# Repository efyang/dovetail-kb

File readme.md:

# Dovetail Keyboard

Uses a modified version of ergogen that supports placing arbitrary library parts.

### FreeCAD Pics (some parts didn't survive the conversion process)

## Features

-   underglow
-   trackpad (tm035035-2024-003)
-   solder-on 90-degree thumb clusters
-   choc spacing
-   36 keys

To update using ergogen:

-   `node ergogen/src/cli.js ergogen.yaml -o .`
-   Open pcb in pcbnew
-   Tools -> Update Footprints from Library
-   Check all "Update Options"
-   Update

## Parts list

| Qty | Part                       | Info                                                                                          | Link(s)                                                   |     |
| --- | -------------------------- | --------------------------------------------------------------------------------------------- | --------------------------------------------------------- | --- |
| 2   | KB2040                     | QMK compatible pro-micro footprint. Currently must have QMK for trackpad, recommmended RP2040 | https://www.adafruit.com/product/5302                     |     |
| 2   | PJ-320A Jack               |                                                                                               | https://www.aliexpress.com/item/2251832181971069.html     |     |
| 36  | Kailh Choc Hotswap Sockets |                                                                                               | https://www.aliexpress.com/item/3256803389452947.html     |     |
| 3   | M2 Standoffs               | Trying M2x7                                                                                   | https://www.aliexpress.com/item/2251832782516182.html     |     |
| idk can't count   | M2 Screws                  |                                                                                               |                                                           |     |
| 1   | FPC Cable                  | 0.5mm pitch, 12pin, same side (but probably should cut and strip yourself anyways)            | https://www.aliexpress.com/item/3256801417741263.html     |     |
| 1   | FPC Connector              | 12P, 0.5mm pitch                                                                              | https://www.aliexpress.com/item/2261800162045502.html     |     |
| 4   | MCU Sockets (optional)     | I like these ones - PH3.5, use them with regular headers                                      | https://www.aliexpress.com/item/2251832713321083.html     |     |
| 2   | Scroll Wheel               |                                                                                               | https://www.aliexpress.com/item/2251832804635444.html     |     |
| 14  | WS2812b 5050               |                                                                                               | https://www.aliexpress.com/item/3256802466699315.html     |     |
| 1   | TM035035-2024-003 Trackpad | Cirque Glide Trackpad with overlay                                                            | https://www.mouser.com/ProductDetail/355-TM0350352024-003 |     |
| 2   | EVQ-P7C01P Reset Switch    | I wanted to be fancy lol                                                                      | https://www.mouser.com/ProductDetail/667-EVQP7C01P        |     |
| 1   | Trackpad holder part       | Probably want 2 just in case                                                                  | [In repo](Models/trackpad-holder-Fusion.stl)              |     |
| 1   | 1 of each PCB minimum      | left-main, right-main, left-thumb, right-thumb (you could actually interchange the thumbs)    | [In repo](gerbers)                                        |     |
| 2   | Plates        | Untested                                                                                           | [In repo](outlines/cutout_with_holes.dxf)                                                          |     |
| 12   | M2 standoffs (5mm)         | Untested                                                                                           | https://www.aliexpress.com/item/2251832782591461.html                                                          |     |
| 2  | 1/4in lock nut         | Untested                                                                                           | https://www.aliexpress.com/item/3256802483856268.html                                                          |     |
| 2  | Camera swivel thingy        | Untested                                                                                           | https://www.aliexpress.com/item/3256803400603212.html                                                          |     |
| 2  | Magnetic Base        | Untested                                                                                           | https://www.aliexpress.com/item/3256803496352836.html                                                          |     |
| 2  | Palm LED Diffuser | Untested                                                                                           | [In repo](outlines/palm_led_diffuser_final.dxf)                                                          |     |
| 2  | Palm LED Diffuser Spacer | Untested                                                                                           | [In repo](outlines/palm_led_diffuser_spacer.dxf)                                                          |     |
| 36  | Diodes           |                                                                                               |      |     |
| 1   | Case (optional)            |                                                                                               | https://www.aliexpress.com/item/3256803532895347.html     |     |

## Notes

-   Designed for 3.3v power/logic (kb2040)
    -   if you want to use 5v then you have to desolder more on the trackpad pcb
-   Rectangular size (at most): ~ 14cmx11cmx5.5cm

## Inspo/Useful Links
- https://www.reddit.com/r/ErgoMechKeyboards/comments/uq2yyq/kyria_with_cirque_circle_trackpad/
- https://github.com/macroxue/keyboard-tenting
- https://www.reddit.com/r/PeripheralDesign/comments/uk9l94/trackball_emulation_on_cirque_glidepoint_circle/
- https://www.cirque.com/message-board?p=post%2Fusing-the-cirque-tm035035-and-tm040040-circle-trackpads-in-5v-systems-10126328
- https://github.com/dkao/qmk_firmware/commits/cirque_trackpad_features
- https://www.thingiverse.com/thing:5385829/files
- https://github.com/Bastardkb/dilemma

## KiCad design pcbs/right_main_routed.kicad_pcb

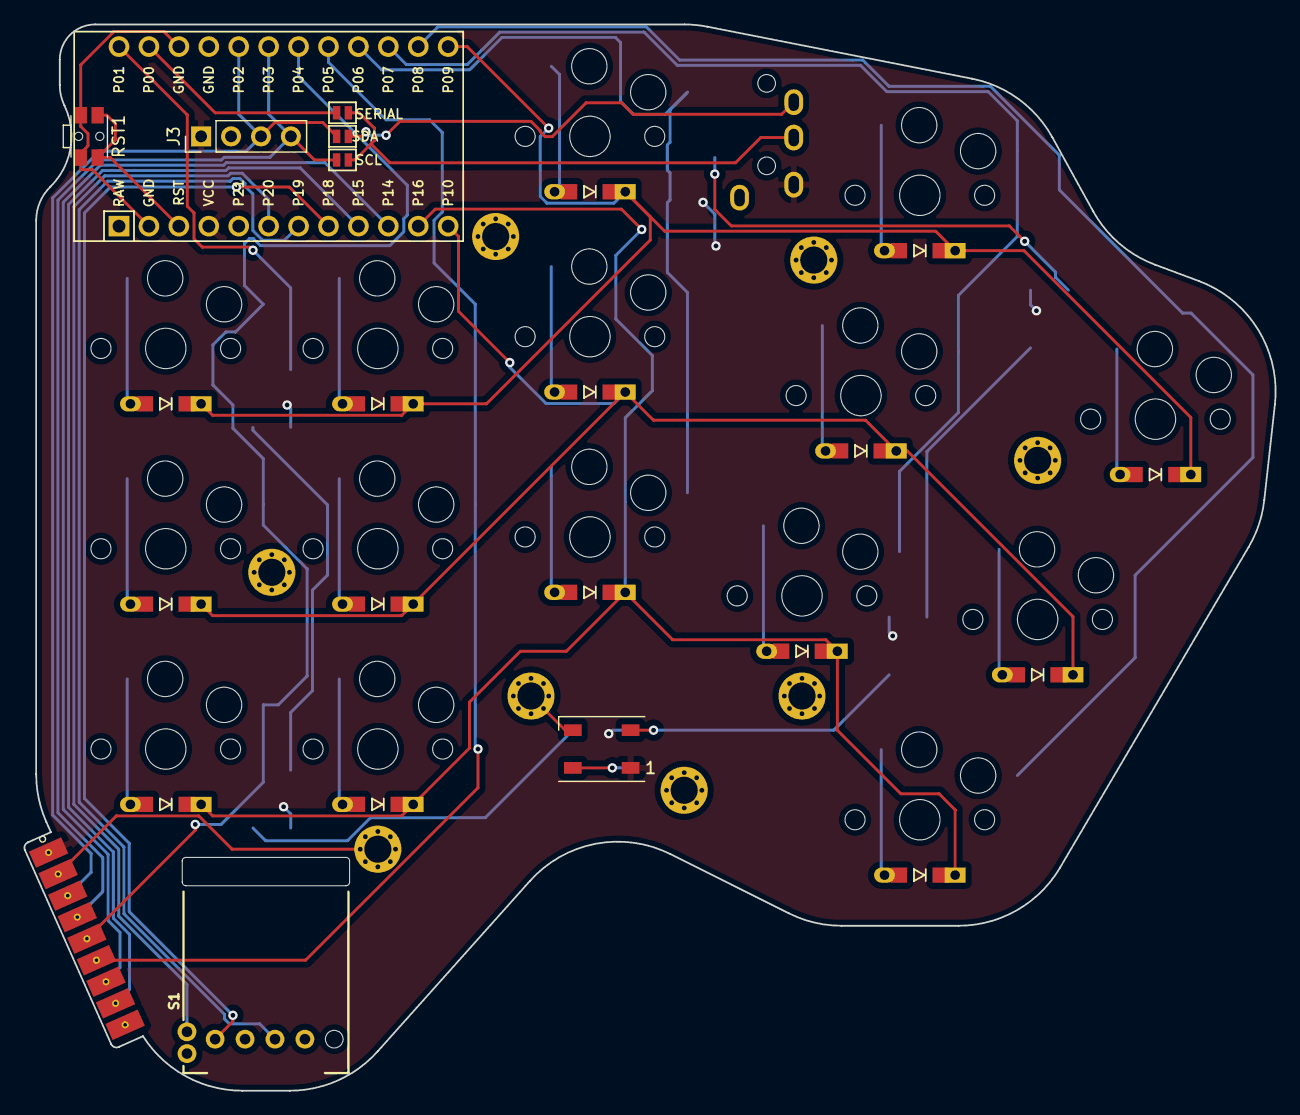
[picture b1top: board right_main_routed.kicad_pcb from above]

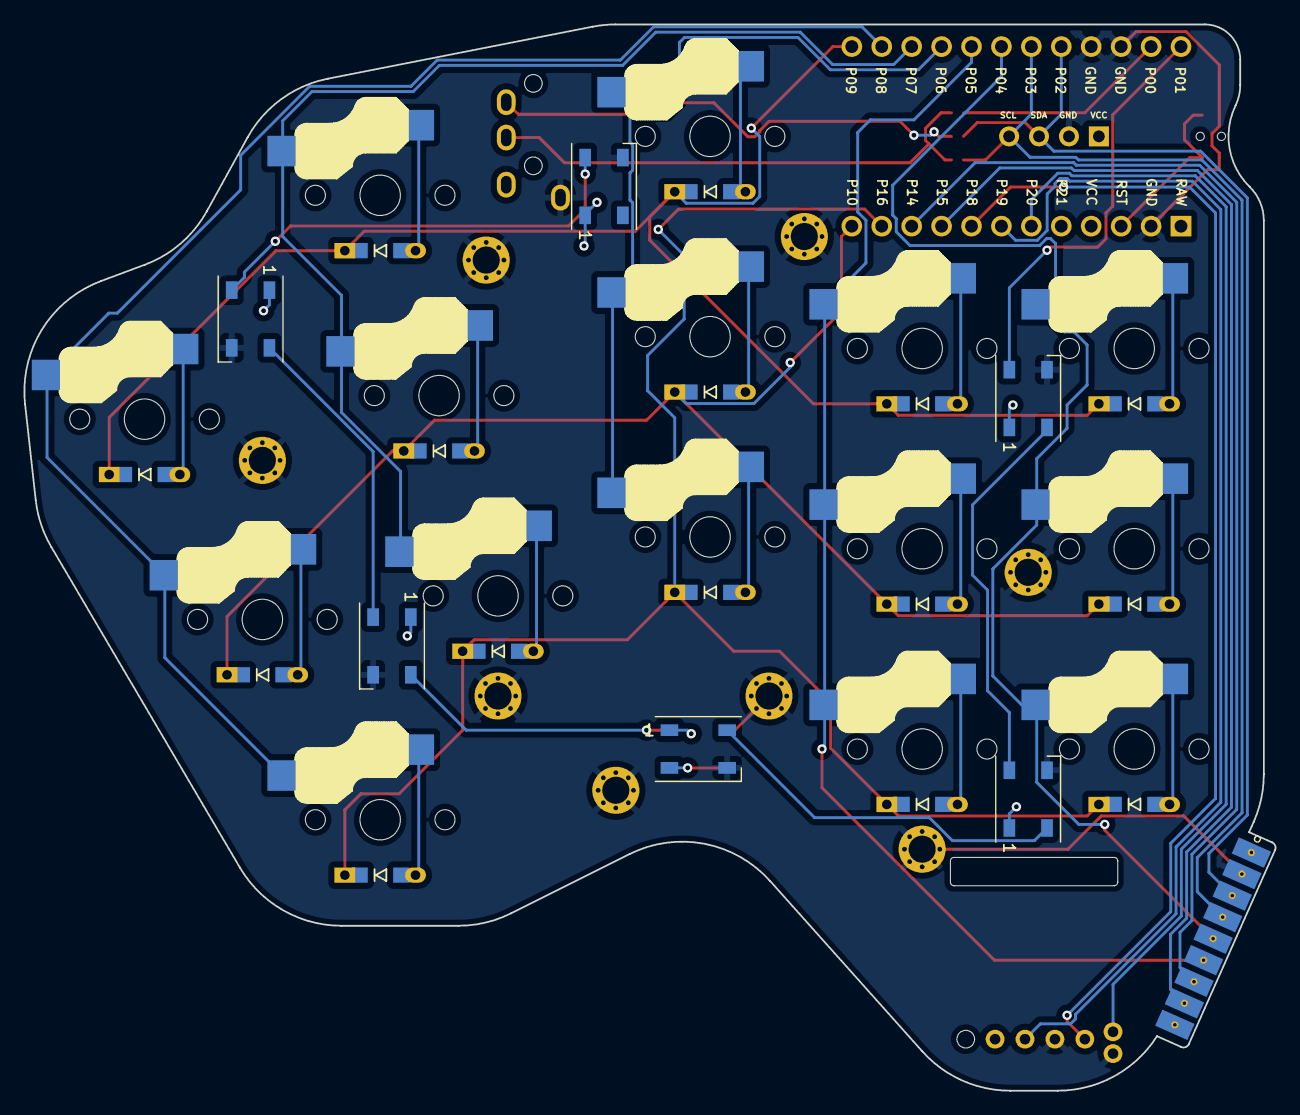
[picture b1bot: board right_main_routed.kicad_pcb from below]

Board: 2 copper layers, 106.2 x 90.5 mm, 54 parts (6 on the bottom side), 43 nets.

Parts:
D1, D2, D3, D4, D5, D6, D7, D8, D9, D10, D11, D12, D13, D14, D15: Diode; D3_TH_SMD_v2
DS1, DS2, DS3, DS4, DS5, DS6, DS7: WS2812b; LED_WS2812B_PLCC4_5.0x5.0mm_P3.2mm
H1, H3, H5, H7, H9, H11, H13, H15: M2; M2_HOLE_v3
J1: TRRS; TRRS-PJ-320A
J3: I2C Breakout; PinHeader_1x04_P2.54mm_Vertical
J5: SERIAL; Jumper
J6: SDA; Jumper
J7: SCL; Jumper
J14: Male 9pin; kb_90deg_connector_male_9pin
RST1: RST; SW_SPST_EVQP7C
S1: Scroll Wheel; EVQWGD001
SW1, SW2, SW3, SW4, SW5, SW6, SW7, SW8, SW9, SW10, SW11, SW12, SW13, SW14, SW15: Val**; PG1350
U1: Pro Micro Footprint; ProMicro

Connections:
C1: J14.5, SW1.2, SW2.2, SW3.2, U1.19
C2: J14.6, SW4.2, SW5.2, SW6.2, U1.20
C3: SW7.2, SW8.2, SW9.2, U1.21
C4: SW10.2, SW11.2, SW12.2, U1.22
C5: SW13.2, SW14.2, SW15.2, U1.23
GND: DS1.3, DS2.3, DS3.3, DS4.3, DS5.3, DS6.3, DS7.3, H1.1, H3.1, H5.1, H7.1, H9.1, H11.1, H13.1, H15.1, J1.1, J3.2, J14.2, RST1.2, S1.B, S1.S1, U1.2, U1.15, U1.16
R1: D3.1, D6.1, D9.1, D12.1, D15.1, U1.24
R2: D2.1, D5.1, D8.1, D11.1, D14.1, U1.12
R3: D1.1, D4.1, D7.1, D10.1, D13.1, U1.11
R4: J14.7, U1.10
R5: J14.8, U1.9
RGB: DS1.4, U1.13
RST: RST1.1, U1.3
SCL: J3.4, J7.1, J14.4, U1.18
SDA: J3.3, J6.1, J14.3, U1.17
SERIAL: J5.1, U1.14
TRRS3: J1.3, J5.2, J7.2
TRRS4: J1.4, J6.2
VCC: DS1.1, DS2.1, DS3.1, DS4.1, DS5.1, DS6.1, DS7.1, J1.2, J3.1, J14.1, U1.4
far_bottom: D1.2, SW1.1
far_home: D2.2, SW2.1
far_top: D3.2, SW3.1
index_bottom: D4.2, SW4.1
index_home: D5.2, SW5.1
index_top: D6.2, SW6.1
middle_bottom: D7.2, SW7.1
middle_home: D8.2, SW8.1
middle_top: D9.2, SW9.1
pinkie_bottom: D13.2, SW13.1
pinkie_home: D14.2, SW14.1
pinkie_top: D15.2, SW15.1
rgb_palm_out: DS4.2, DS5.4
rgb_ug1_out: DS1.2, DS2.4
rgb_ug2_out: DS2.2, DS3.4
rgb_ug3_out: DS3.2, DS4.4
rgb_ug4_out: DS5.2, DS6.4
rgb_ug5_out: DS6.2, DS7.4
ring_bottom: D10.2, SW10.1
ring_home: D11.2, SW11.1
ring_top: D12.2, SW12.1
scroll_r1: S1.A, U1.8
scroll_r2: S1.C, U1.7
scroll_switch: S1.S2, U1.6

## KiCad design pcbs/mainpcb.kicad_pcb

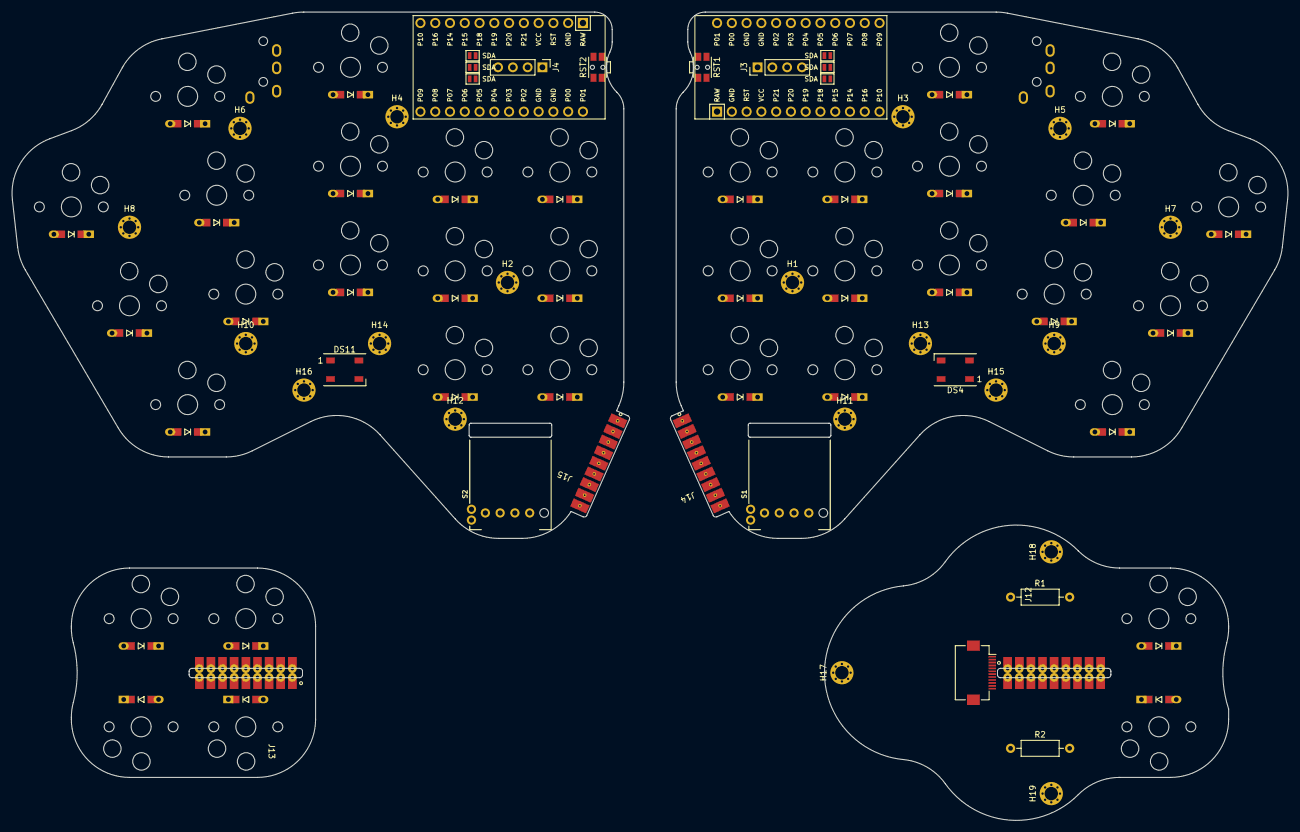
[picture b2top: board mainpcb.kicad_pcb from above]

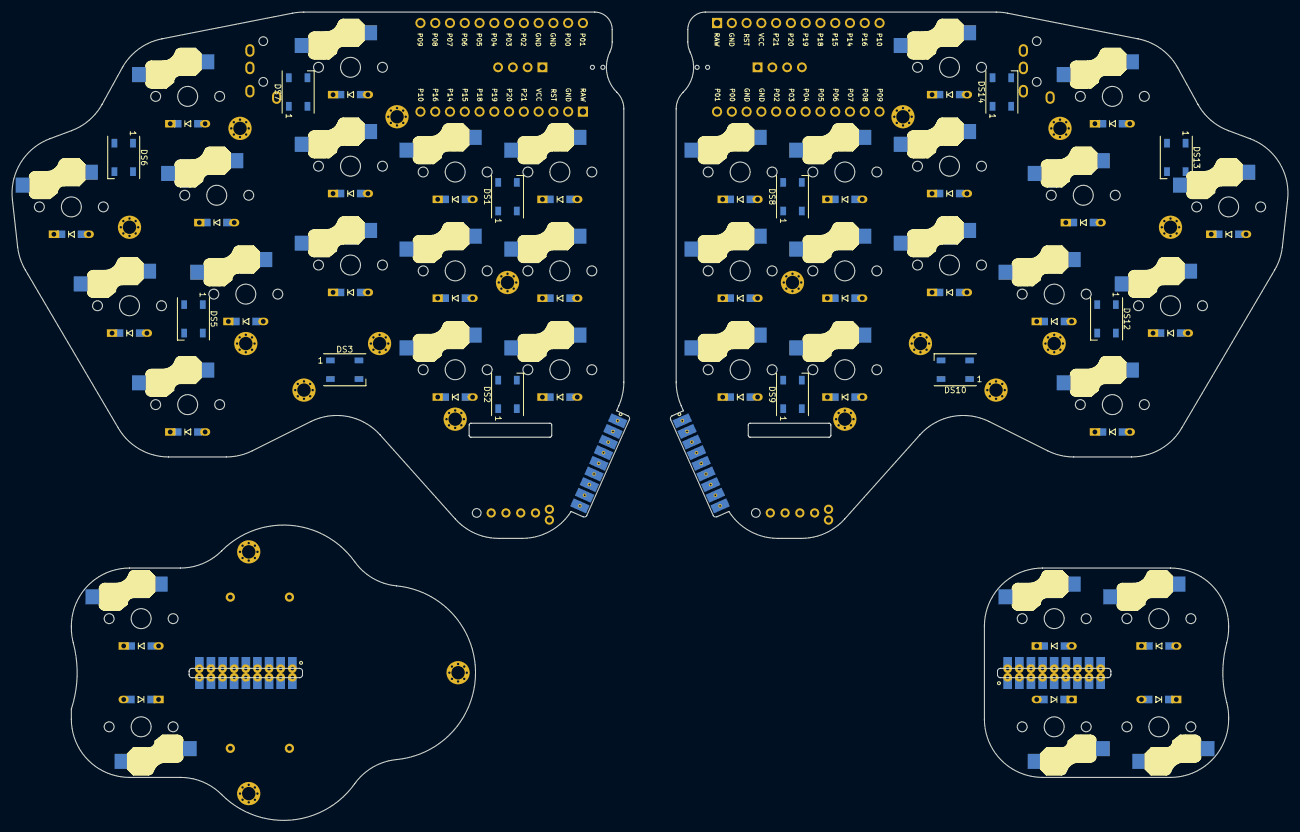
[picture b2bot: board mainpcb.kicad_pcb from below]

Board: 2 copper layers, 219.4 x 139.0 mm, 128 parts (12 on the bottom side), 65 nets, no tracks yet.

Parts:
D1, D2, D3, D4, D5, D6, D7, D8, D9, D10, D11, D12, D13, D14, D15, D16, D17, D18, D19, D20, D21, D22, D23, D24, D25, D26, D27, D28, D29, D30, D31, D32, D33, D34, D35, D36: Diode; D3_TH_SMD_v2
DS1, DS2, DS3, DS4, DS5, DS6, DS7, DS8, DS9, DS10, DS11, DS12, DS13, DS14: WS2812b; LED_WS2812B_PLCC4_5.0x5.0mm_P3.2mm
H1, H2, H3, H4, H5, H6, H7, H8, H9, H10, H11, H12, H13, H14, H15, H16, H17, H18, H19: M2; M2_HOLE_v3
J1, J2: TRRS; TRRS-PJ-320A
J3, J4: I2C Breakout; PinHeader_1x04_P2.54mm_Vertical
J5, J6, J7, J8, J9, J10: SDA; Jumper
J11: 12pin FPC; Hirose_FH12-12S-0.5SH_1x12-1MP_P0.50mm_Horizontal
J12, J13: Female 9pin; kb_90deg_connector_female_9pin
J14, J15: Male 9pin; kb_90deg_connector_male_9pin
R1, R2: 4K7; R_Axial_DIN0207_L6.3mm_D2.5mm_P10.16mm_Horizontal
RST1, RST2: RST; SW_SPST_EVQP7C
S1, S2: Scroll Wheel; EVQWGD001
SW1, SW2, SW3, SW4, SW5, SW6, SW7, SW8, SW9, SW10, SW11, SW12, SW13, SW14, SW15, SW16, SW17, SW18, SW19, SW20, SW21, SW22, SW23, SW24, SW25, SW26, SW27, SW28, SW29, SW30, SW31, SW32, SW33, SW34, SW35, SW36: Val**; PG1350
U1, U2: Pro Micro Footprint; ProMicro

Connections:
C1: J12.5, J13.5, J14.5, J15.5, SW1.2, SW2.2, SW3.2, SW16.2, SW18.2, SW19.2, SW20.2, SW33.2, SW34.2, U1.19, U2.19
C2: J12.6, J13.6, J14.6, J15.6, SW4.2, SW5.2, SW6.2, SW17.2, SW21.2, SW22.2, SW23.2, SW35.2, SW36.2, U1.20, U2.20
C3: SW7.2, SW8.2, SW9.2, SW24.2, SW25.2, SW26.2, U1.21, U2.21
C4: SW10.2, SW11.2, SW12.2, SW27.2, SW28.2, SW29.2, U1.22, U2.22
C5: SW13.2, SW14.2, SW15.2, SW30.2, SW31.2, SW32.2, U1.23, U2.23
GND: DS1.3, DS2.3, DS3.3, DS4.3, DS5.3, DS6.3, DS7.3, DS8.3, DS9.3, DS10.3, DS11.3, DS12.3, DS13.3, DS14.3, H1.1, H2.1, H3.1, H4.1, H5.1, H6.1, H7.1, H8.1, H9.1, H10.1, H11.1, H12.1, H13.1, H14.1, H15.1, H16.1, H17.1, H18.1, H19.1, J1.1, J2.1, J3.2, J4.2, J11.2, J12.2, J13.2, J14.2, J15.2, RST1.2, RST2.2, S1.B, S1.S1, S2.B, S2.S1, U1.2, U1.15, U1.16, U2.2, U2.15, U2.16
R1: D3.1, D6.1, D9.1, D12.1, D15.1, D20.1, D23.1, D26.1, D29.1, D32.1, U1.24, U2.24
R2: D2.1, D5.1, D8.1, D11.1, D14.1, D19.1, D22.1, D25.1, D28.1, D31.1, U1.12, U2.12
R3: D1.1, D4.1, D7.1, D10.1, D13.1, D18.1, D21.1, D24.1, D27.1, D30.1, U1.11, U2.11
R4: D16.1, D17.1, D33.1, D35.1, J12.7, J13.7, J14.7, J15.7, U1.10, U2.10
R5: D34.1, D36.1, J12.8, J13.8, J14.8, J15.8, U1.9, U2.9
RGB: DS1.4, DS8.4, U1.13, U2.13
RST: RST1.1, RST2.1, U1.3, U2.3
SCL: J3.4, J4.4, J7.1, J10.1, J11.4, J12.4, J13.4, J14.4, J15.4, R2.2, U1.18, U2.18
SDA: J3.3, J4.3, J6.1, J9.1, J11.3, J12.3, J13.3, J14.3, J15.3, R1.2, U1.17, U2.17
SERIAL: J5.1, J8.1, U1.14, U2.14
TRRS3: J1.3, J2.3, J5.2, J7.2, J8.2, J10.2
TRRS4: J1.4, J2.4, J6.2, J9.2
VCC: DS1.1, DS2.1, DS3.1, DS4.1, DS5.1, DS6.1, DS7.1, DS8.1, DS9.1, DS10.1, DS11.1, DS12.1, DS13.1, DS14.1, J1.2, J2.2, J3.1, J4.1, J11.1, J12.1, J13.1, J14.1, J15.1, R1.1, R2.1, U1.4, U2.4
c1_r4: D16.2, SW16.1
c2_r4: D17.2, SW17.1
far_bottom: D1.2, SW1.1
far_home: D2.2, SW2.1
far_top: D3.2, SW3.1
index_bottom: D4.2, SW4.1
index_home: D5.2, SW5.1
index_top: D6.2, SW6.1
middle_bottom: D7.2, SW7.1
middle_home: D8.2, SW8.1
middle_top: D9.2, SW9.1
mirror_c1_r4: D33.2, SW33.1
mirror_c1_r5: D34.2, SW34.1
mirror_c2_r4: D35.2, SW35.1
mirror_c2_r5: D36.2, SW36.1
mirror_far_bottom: D18.2, SW18.1
mirror_far_home: D19.2, SW19.1
mirror_far_top: D20.2, SW20.1
mirror_index_bottom: D21.2, SW21.1
mirror_index_home: D22.2, SW22.1
mirror_index_top: D23.2, SW23.1
mirror_middle_bottom: D24.2, SW24.1
mirror_middle_home: D25.2, SW25.1
mirror_middle_top: D26.2, SW26.1
mirror_pinkie_bottom: D30.2, SW30.1
mirror_pinkie_home: D31.2, SW31.1
mirror_pinkie_top: D32.2, SW32.1
mirror_ring_bottom: D27.2, SW27.1
mirror_ring_home: D28.2, SW28.1
mirror_ring_top: D29.2, SW29.1
pinkie_bottom: D13.2, SW13.1
pinkie_home: D14.2, SW14.1
pinkie_top: D15.2, SW15.1
rgb_palm_out: DS4.2, DS5.4, DS11.2, DS12.4
rgb_ug1_out: DS1.2, DS2.4, DS8.2, DS9.4
rgb_ug2_out: DS2.2, DS3.4, DS9.2, DS10.4
rgb_ug3_out: DS3.2, DS4.4, DS10.2, DS11.4
rgb_ug4_out: DS5.2, DS6.4, DS12.2, DS13.4
rgb_ug5_out: DS6.2, DS7.4, DS13.2, DS14.4
rgb_ug6_out: DS7.2, DS14.2
ring_bottom: D10.2, SW10.1
ring_home: D11.2, SW11.1
ring_top: D12.2, SW12.1
scroll_r1: S1.A, S2.A, U1.8, U2.8
scroll_r2: S1.C, S2.C, U1.7, U2.7
scroll_switch: S1.S2, S2.S2, U1.6, U2.6

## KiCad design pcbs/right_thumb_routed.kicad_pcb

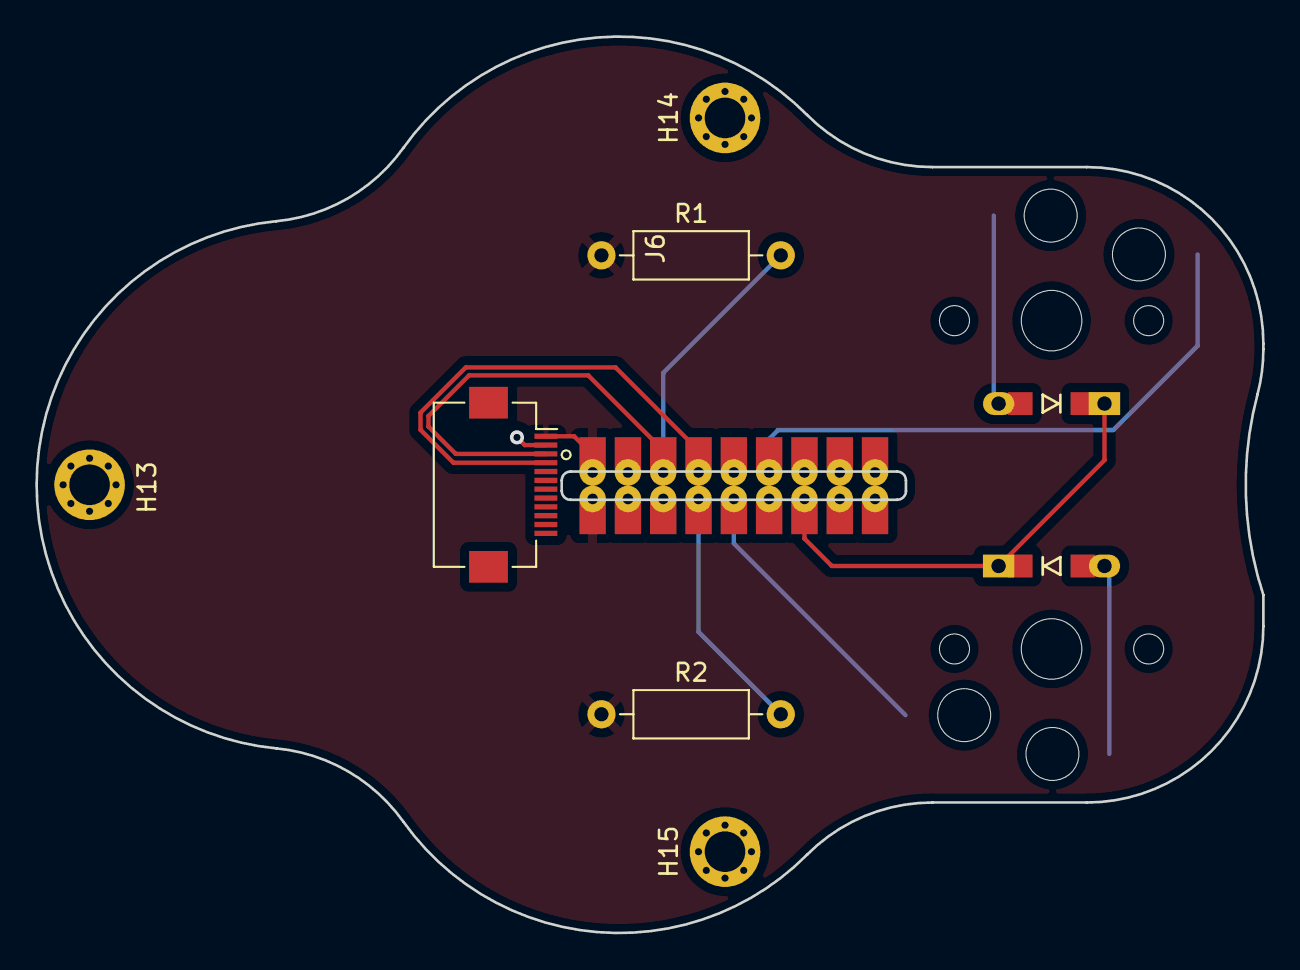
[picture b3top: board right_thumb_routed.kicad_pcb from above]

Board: 2 copper layers, 69.5 x 50.8 mm, 11 parts (0 on the bottom side), 9 nets.

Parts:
D16, D17: Diode; D3_TH_SMD_v2
H13, H14, H15: M2; M2_HOLE_v3
J5: 12pin FPC; Hirose_FH12-12S-0.5SH_1x12-1MP_P0.50mm_Horizontal
J6: Female 9pin; kb_90deg_connector_female_9pin
R1, R2: 4K7; R_Axial_DIN0207_L6.3mm_D2.5mm_P10.16mm_Horizontal
SW16, SW17: Val**; PG1350

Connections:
C1: J6.5, SW16.2
C2: J6.6, SW17.2
GND: H13.1, H14.1, H15.1, J5.2, J6.2
R4: D16.1, D17.1, J6.7
SCL: J5.4, J6.4, R2.2
SDA: J5.3, J6.3, R1.2
VCC: J5.1, J6.1, R1.1, R2.1
c1_r4: D16.2, SW16.1
c2_r4: D17.2, SW17.1

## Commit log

2022-07-27 Version 1 layout?
2022-07-28 I can't believe I learned freecad for this + mounting holes
2022-07-28 Hopefully finalized layout + more pretty pics and cad
2022-07-28 Add resistors
2022-07-28 Finish fillets
2022-07-29 Finish v1 with gerbers?
2022-08-01 Update readme with parts
2022-08-02 Add plate generator
2022-09-03 Add palm led diffuser
2022-09-20 Update trackpad holder
